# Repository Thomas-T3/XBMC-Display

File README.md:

# XBMC-Display
Bordcomputer für T3 mit AGG

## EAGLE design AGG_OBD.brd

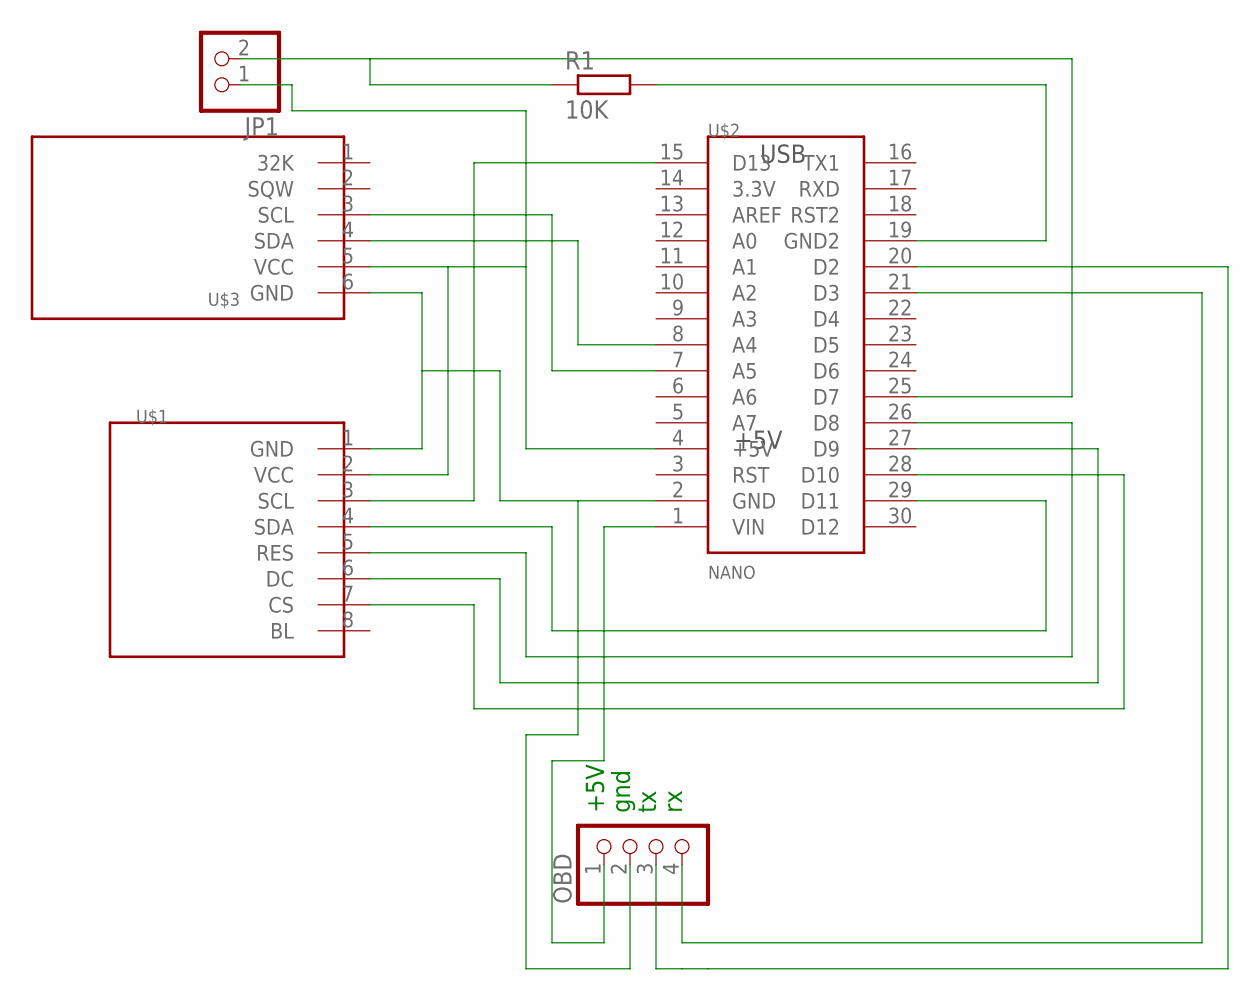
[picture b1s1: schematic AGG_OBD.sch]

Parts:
JP1: PINHD-1X2; 1X02
OBD: PINHD-1X4; 1X04
R1: 10K; 0207/5V
U$1: DISPLAY_TFT_LCD_128X160; DISPLAYTFT_LCD128X160
U$2: NANO
U$3: DS3231DS3231; DS3231

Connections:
unnamed: U$1.5 (RES), U$2.26 (D8)
unnamed: JP1.1, U$1.2 (VCC), U$2.4 (+5V), U$3.5 (VCC)
unnamed: U$1.6 (DC), U$2.27 (D9)
unnamed: U$2.7 (A5), U$3.3 (SCL)
unnamed: U$2.8 (A4), U$3.4 (SDA)
unnamed: U$1.3 (SCL), U$2.15 (D13)
unnamed: U$1.4 (SDA), U$2.29 (D11)
unnamed: U$1.7 (CS), U$2.28 (D10)
unnamed: JP1.2, R1.1, U$2.25 (D7)
unnamed: R1.2, U$2.19 (GND2)
unnamed: OBD.1, U$2.1 (VIN)
unnamed: OBD.2, U$1.1 (GND), U$2.2 (GND), U$3.6 (GND)
unnamed: OBD.4, U$2.21 (D3)
unnamed: OBD.3, U$2.20 (D2)

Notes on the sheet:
+5V
gnd

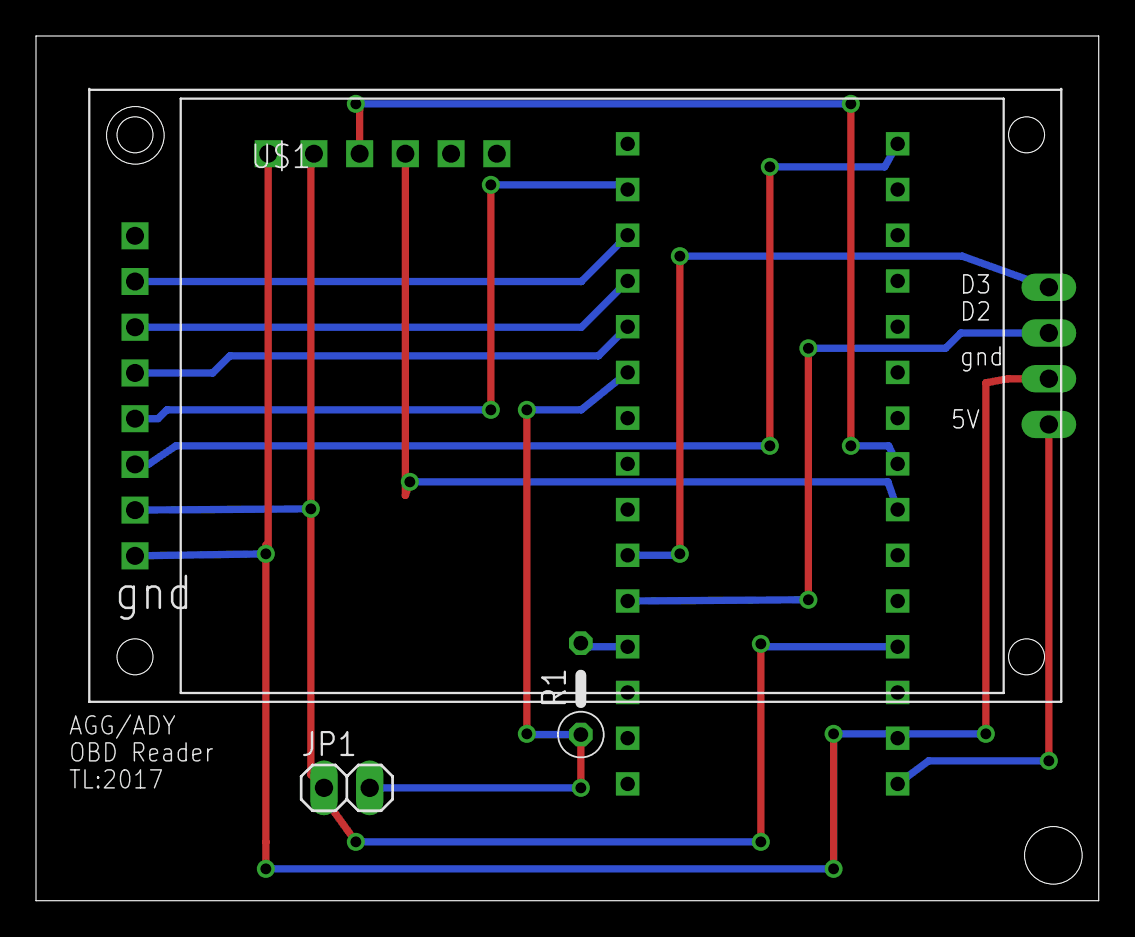
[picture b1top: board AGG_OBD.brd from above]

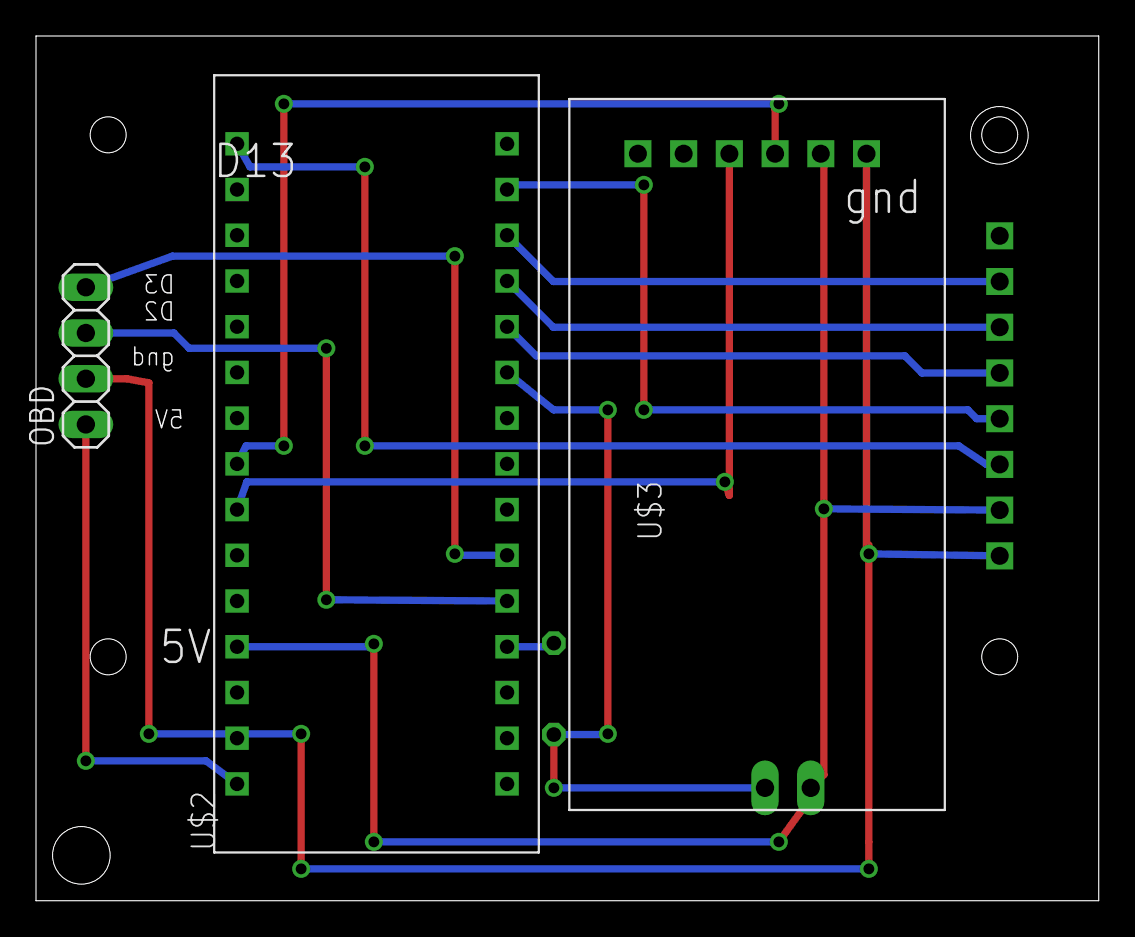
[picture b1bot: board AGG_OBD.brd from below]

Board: 2 copper layers, 59.0 x 48.0 mm, 6 parts (3 on the bottom side), 14 nets.
